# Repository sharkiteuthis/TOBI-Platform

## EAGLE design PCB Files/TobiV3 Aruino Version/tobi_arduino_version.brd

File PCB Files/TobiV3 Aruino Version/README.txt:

Bottom Copper		GBL
Bottom Silkscreen	GBO
Bottom Soldermask	GBS
Top Copper		GTL
Top Silkscreen		GTO
Top Soldermask		GTS
Drill File		TXT
Drill Station Info File	dri
Photoplotter Info File	gpi
Mill Layer		GML
Top Paste		GTP

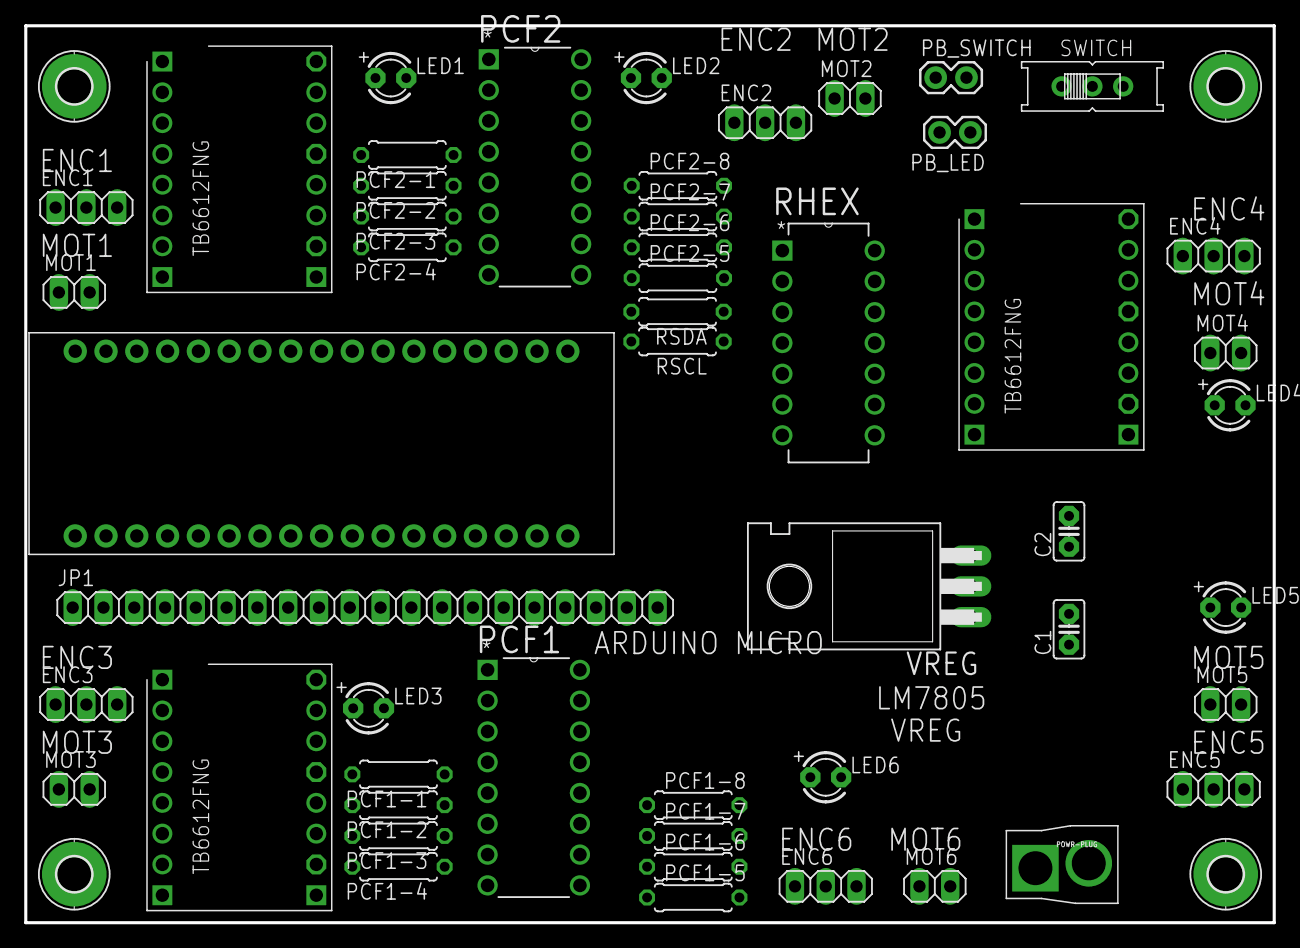
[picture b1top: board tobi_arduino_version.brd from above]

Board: 2 copper layers, 103.0 x 74.0 mm, 55 parts (0 on the bottom side), 64 nets, no tracks yet.

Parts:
ARDUINOMICRO: ARDUINOMICRO
C1: 0.33; C025-025X050
C2: 0.1; C025-025X050
DRIVER1, DRIVER2, DRIVER3: POLOLU_MOTOR_DRV8835THROUGHHOLE; POLOLU_MOTOR_DRV_DRV8835
ENC1, ENC2, ENC3, ENC4, ENC5, ENC6: 1X03
H1, H2, H3, H4: MOUNT-PAD-ROUND2.8; 2,8-PAD
JP1: 1X20
LED1, LED2, LED3, LED4, LED5, LED6: LED3MM
MOT1, MOT2, MOT3, MOT4, MOT5, MOT6: 1X02
PB_LED: M02PTH; 1X02
PB_SWITCH: M02PTH; 1X02
PCF1, PCF2: PCF8574AN; DIP254P762X508-16
PCF1-1, PCF1-2, PCF1-3, PCF1-4, PCF1-5, PCF1-6, PCF1-7, PCF1-8, PCF2-1, PCF2-2, PCF2-3, PCF2-4, PCF2-5, PCF2-6, PCF2-7, PCF2-8: 0207/7
POWR-PLUG: MINI_DEANSSMD; MINI_DEANS
RHEX: SN74HC04N; DIP254P762X508-14
RSCL: 0207/7
RSDA: 0207/7
SWITCH: EG1218
VREG: 7805T; TO220H

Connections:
D4: ARDUINOMICRO.P$9, JP1.10
D7: ARDUINOMICRO.P$6, JP1.8
D8: ARDUINOMICRO.P$5, JP1.9
D13: ARDUINOMICRO.P$34, JP1.11
GND: ARDUINOMICRO.P$21, C1.2, C2.2, DRIVER1.GND, DRIVER1.GND2, DRIVER1.GND3, DRIVER2.GND, DRIVER2.GND2, DRIVER2.GND3, DRIVER3.GND, DRIVER3.GND2, DRIVER3.GND3, ENC1.2, ENC2.2, ENC3.2, ENC4.2, ENC5.2, ENC6.2, H1.B2,8, H2.B2,8, H3.B2,8, H4.B2,8, JP1.1, LED1.K, LED2.K, LED3.K, LED4.K, LED5.K, LED6.K, PB_LED.2, PB_SWITCH.1, PCF1.1, PCF1.2, PCF1.3, PCF1.8, PCF2.2, PCF2.3, PCF2.8, POWR-PLUG.GND, RHEX.7, VREG.2
LED1: LED1.A, PCF2.5, PCF2-2.1
LED2: LED2.A, PCF2.6, PCF2-3.1
LED3: LED3.A, PCF2.7, PCF2-4.1
LED4: LED4.A, PCF2.9, PCF2-5.1
LED5: LED5.A, PCF2.10, PCF2-6.1
LED6: LED6.A, PCF2.11, PCF2-7.1
M1_A: DRIVER1.AO1, MOT1.1
M1_B: DRIVER1.AO2, MOT1.2
M1_ENC: ARDUINOMICRO.P$31, ENC1.3
M1_IN1: DRIVER1.AIN1, PCF1.4, PCF1-1.1, RHEX.1
M1_IN2: DRIVER1.AIN2, RHEX.2
M1_M2_EN: DRIVER1.STBY, PCF1.11, PCF1-7.1
M1_PWM: ARDUINOMICRO.P$4, DRIVER1.PWMA, JP1.2
M2_A: DRIVER1.BO1, MOT2.1
M2_B: DRIVER1.BO2, MOT2.2
M2_ENC: ARDUINOMICRO.P$30, ENC2.3
M2_IN1: DRIVER1.BIN1, PCF1.5, PCF1-2.1, RHEX.3
M2_IN2: DRIVER1.BIN2, RHEX.4
M2_PWM: ARDUINOMICRO.P$8, DRIVER1.PWMB, JP1.3
M3_A: DRIVER2.AO1, MOT3.1
M3_B: DRIVER2.AO2, MOT3.2
M3_ENC: ARDUINOMICRO.P$29, ENC3.3
M3_IN1: DRIVER2.AIN1, PCF1.6, PCF1-3.1, RHEX.5
M3_IN2: DRIVER2.AIN2, RHEX.6
M3_M4_EN: DRIVER2.STBY, PCF1.12, PCF1-8.1
M3_PWM: ARDUINOMICRO.P$7, DRIVER2.PWMA, JP1.4
M4_A: DRIVER2.BO1, MOT4.1
M4_B: DRIVER2.BO2, MOT4.2
M4_ENC: ARDUINOMICRO.P$28, ENC4.3
M4_IN1: DRIVER2.BIN1, PCF1.7, PCF1-4.1, RHEX.9
M4_IN2: DRIVER2.BIN2, RHEX.8
M4_PWM: ARDUINOMICRO.P$3, DRIVER2.PWMB, JP1.5
M5_A: DRIVER3.AO1, MOT5.1
M5_B: DRIVER3.AO2, MOT5.2
M5_ENC: ARDUINOMICRO.P$27, ENC5.3
M5_IN1: DRIVER3.AIN1, PCF1.9, PCF1-5.1, RHEX.11
M5_IN2: DRIVER3.AIN2, RHEX.10
M5_M6_EN: DRIVER3.STBY, PCF2.4, PCF2-1.1
M5_PWM: ARDUINOMICRO.P$2, DRIVER3.PWMA, JP1.6
M6_A: DRIVER3.BO1, MOT6.1
M6_B: DRIVER3.BO2, MOT6.2
M6_ENC: ARDUINOMICRO.P$26, ENC6.3
M6_IN1: DRIVER3.BIN1, PCF1.10, PCF1-6.1, RHEX.13
M6_IN2: DRIVER3.BIN2, RHEX.12
M6_PWM: ARDUINOMICRO.P$1, DRIVER3.PWMB, JP1.7
MISO: ARDUINOMICRO.P$19, JP1.15
MOSI: ARDUINOMICRO.P$17, JP1.18
PB_LED: PB_LED.1, PCF2.12, PCF2-8.1
RESET: ARDUINOMICRO.P$22, PB_SWITCH.2
RX: ARDUINOMICRO.P$14, JP1.13
SCK: ARDUINOMICRO.P$18, JP1.16
SCL: ARDUINOMICRO.P$10, PCF1.14, PCF2.14, RSCL.2
SDA: ARDUINOMICRO.P$11, PCF1.15, PCF2.15, RSDA.2
SS: ARDUINOMICRO.P$16, JP1.17
TX: ARDUINOMICRO.P$15, JP1.14
V3.3: ARDUINOMICRO.P$33, JP1.19
VCC: C2.1, DRIVER1.VCC, DRIVER2.VCC, DRIVER3.VCC, ENC1.1, ENC2.1, ENC3.1, ENC4.1, ENC5.1, ENC6.1, JP1.12, PCF1.16, PCF1-1.2, PCF1-2.2, PCF1-3.2, PCF1-4.2, PCF1-5.2, PCF1-6.2, PCF1-7.2, PCF1-8.2, PCF2.1, PCF2.16, PCF2-1.2, PCF2-2.2, PCF2-3.2, PCF2-4.2, PCF2-5.2, PCF2-6.2, PCF2-7.2, PCF2-8.2, RHEX.14, RSCL.1, RSDA.1, VREG.3
V_IN: ARDUINOMICRO.P$20, POWR-PLUG.POW, SWITCH.P
V_MOT: C1.1, DRIVER1.VMOT, DRIVER2.VMOT, DRIVER3.VMOT, JP1.20, SWITCH.O, VREG.1

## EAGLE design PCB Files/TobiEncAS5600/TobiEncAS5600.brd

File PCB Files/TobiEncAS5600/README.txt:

Bottom Copper		GBL
Bottom Silkscreen	GBO
Bottom Soldermask	GBS
Top Copper		GTL
Top Silkscreen		GTO
Top Soldermask		GTS
Drill File		TXT
Drill Station Info File	dri
Photoplotter Info File	gpi
Mill Layer		GML
Top Paste		GTP

Bill of Materials	XLSX
Centroid File		CSV

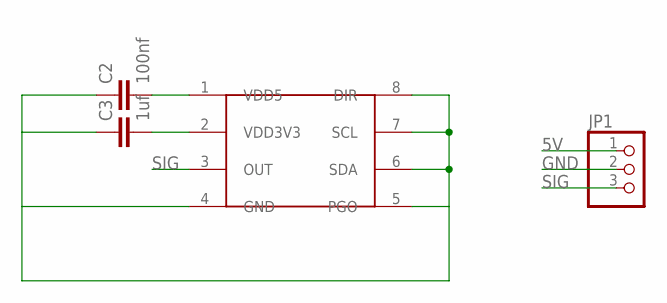
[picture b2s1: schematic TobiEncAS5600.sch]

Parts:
C2: 100nf; 0603-CAP
C3: 1uf; 0603-CAP
JP1: PINHD-1X3; 1X03
U$1: AS5600; SO08

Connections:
5V: C2.2, JP1.1, U$1.1 (VDD5)
GND: C2.1, C3.1, JP1.2, U$1.4 (GND), U$1.5 (PGO), U$1.6 (SDA), U$1.7 (SCL), U$1.8 (DIR)
SIG: JP1.3, U$1.3 (OUT)
VDD3V3: C3.2, U$1.2 (VDD3V3)

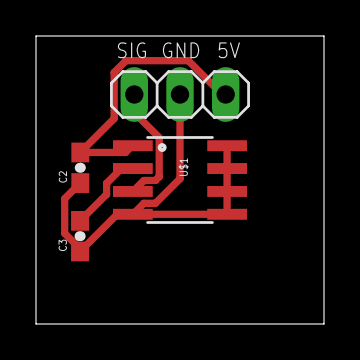
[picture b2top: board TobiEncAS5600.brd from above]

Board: 2 copper layers, 16.0 x 16.0 mm, 4 parts (0 on the bottom side), 4 nets.

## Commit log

2017-12-02 :confetti_ball: Added .gitattributes & .gitignore files
2017-12-02 andrea's 7/10 changes to library
2017-12-14 removed hex encoder, moved to 0-based
2017-12-21 changed pwm pins, added series LED resistors
2017-12-27 fix motor pwm pins
2017-12-27 simple headers for encoders and motors
2018-03-03 moved some components around
2018-03-03 position components for wider encoder board
2018-03-03 double wide encoder board
2018-03-03 add silkscreen to board
2018-03-04 first shot at positioning components
2018-03-04 fix a few things on the silkscreen
2018-03-04 reconciled some nets
2018-03-04 manual routing for scl/sda lines
2018-03-04 hand route sda/scl and thick traces for motor voltage
2018-03-04 hand route gnd
2018-03-05 fix to motor 5 net
2018-03-05 route heavy traces for motor leads
2018-03-07 heavier traces on encoder board since it can accomodate them
2018-03-07 autoroute the rest of the board
2018-03-07 fix silkscreen on pushbutton LED
2018-03-07 rip up main board and try again...
2018-03-07 add ground plane
2018-03-07 add thick traces for battery voltage, motor voltage, sda, scl
2018-03-07 route motor leads with heavy traces
2018-03-08 autoroute the rest, i'm not happy with the vias near pcf1
2018-03-08 manual fixes to the autorouter to connect all the ground planes
2018-04-13 minor silkscreen changes
2018-04-18 add grasp url to board silkscreen
2018-04-29 fix LED hardware bugs
2018-04-29 let's try this again
2018-04-30 no routing
2018-05-04 fix ground plane and autorouter net settings
2018-05-04 used autorouter
2018-05-04 add bottom silkscreen
2018-06-07 try to use the old pcb
2018-07-02 version 3.2 of TOBI mainboard and associated code -- quick turnaround
2018-07-03 tobi v3.3 mainboard
2018-07-05 gerber files and BOM for encoder
2018-07-18 Encoder BOM snd gerber files

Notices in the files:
parts and their libraries:
SparkFun-Capacitors: Licensing: Creative Commons ShareAlike 4.0 International - https://creativecommons.org/licenses/by-sa/4.0
